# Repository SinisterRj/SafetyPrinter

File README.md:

# SafetyPrinter
This project aims to improve the safety of 3D FDM Printers by adding an external MCU (an Arduino) which increases your chance of preventing or mitigating a fire at your home.

_Safety Printer MCU assembly_

The project itself is very simple and designed to be cheap (the minimum needed is an Arduino nano and a few sensors). All you need is some time to assemble everything and test.

This project has a sibling project, the [Octoprint's Safety Printer plugin](https://github.com/SinisterRj/Octoprint_SafetyPrinter) which is optional but it's highly recommended as it helps you monitor your sensors and helps a lot during test phase:

You can find lots of information on [Wiki](https://github.com/SinisterRj/SafetyPrinter/wiki) and we recommend it's reading.

Se você é brasileiro 🇧🇷, junte-se a nós no Discord:
https://discord.gg/3DyXfGwWJY

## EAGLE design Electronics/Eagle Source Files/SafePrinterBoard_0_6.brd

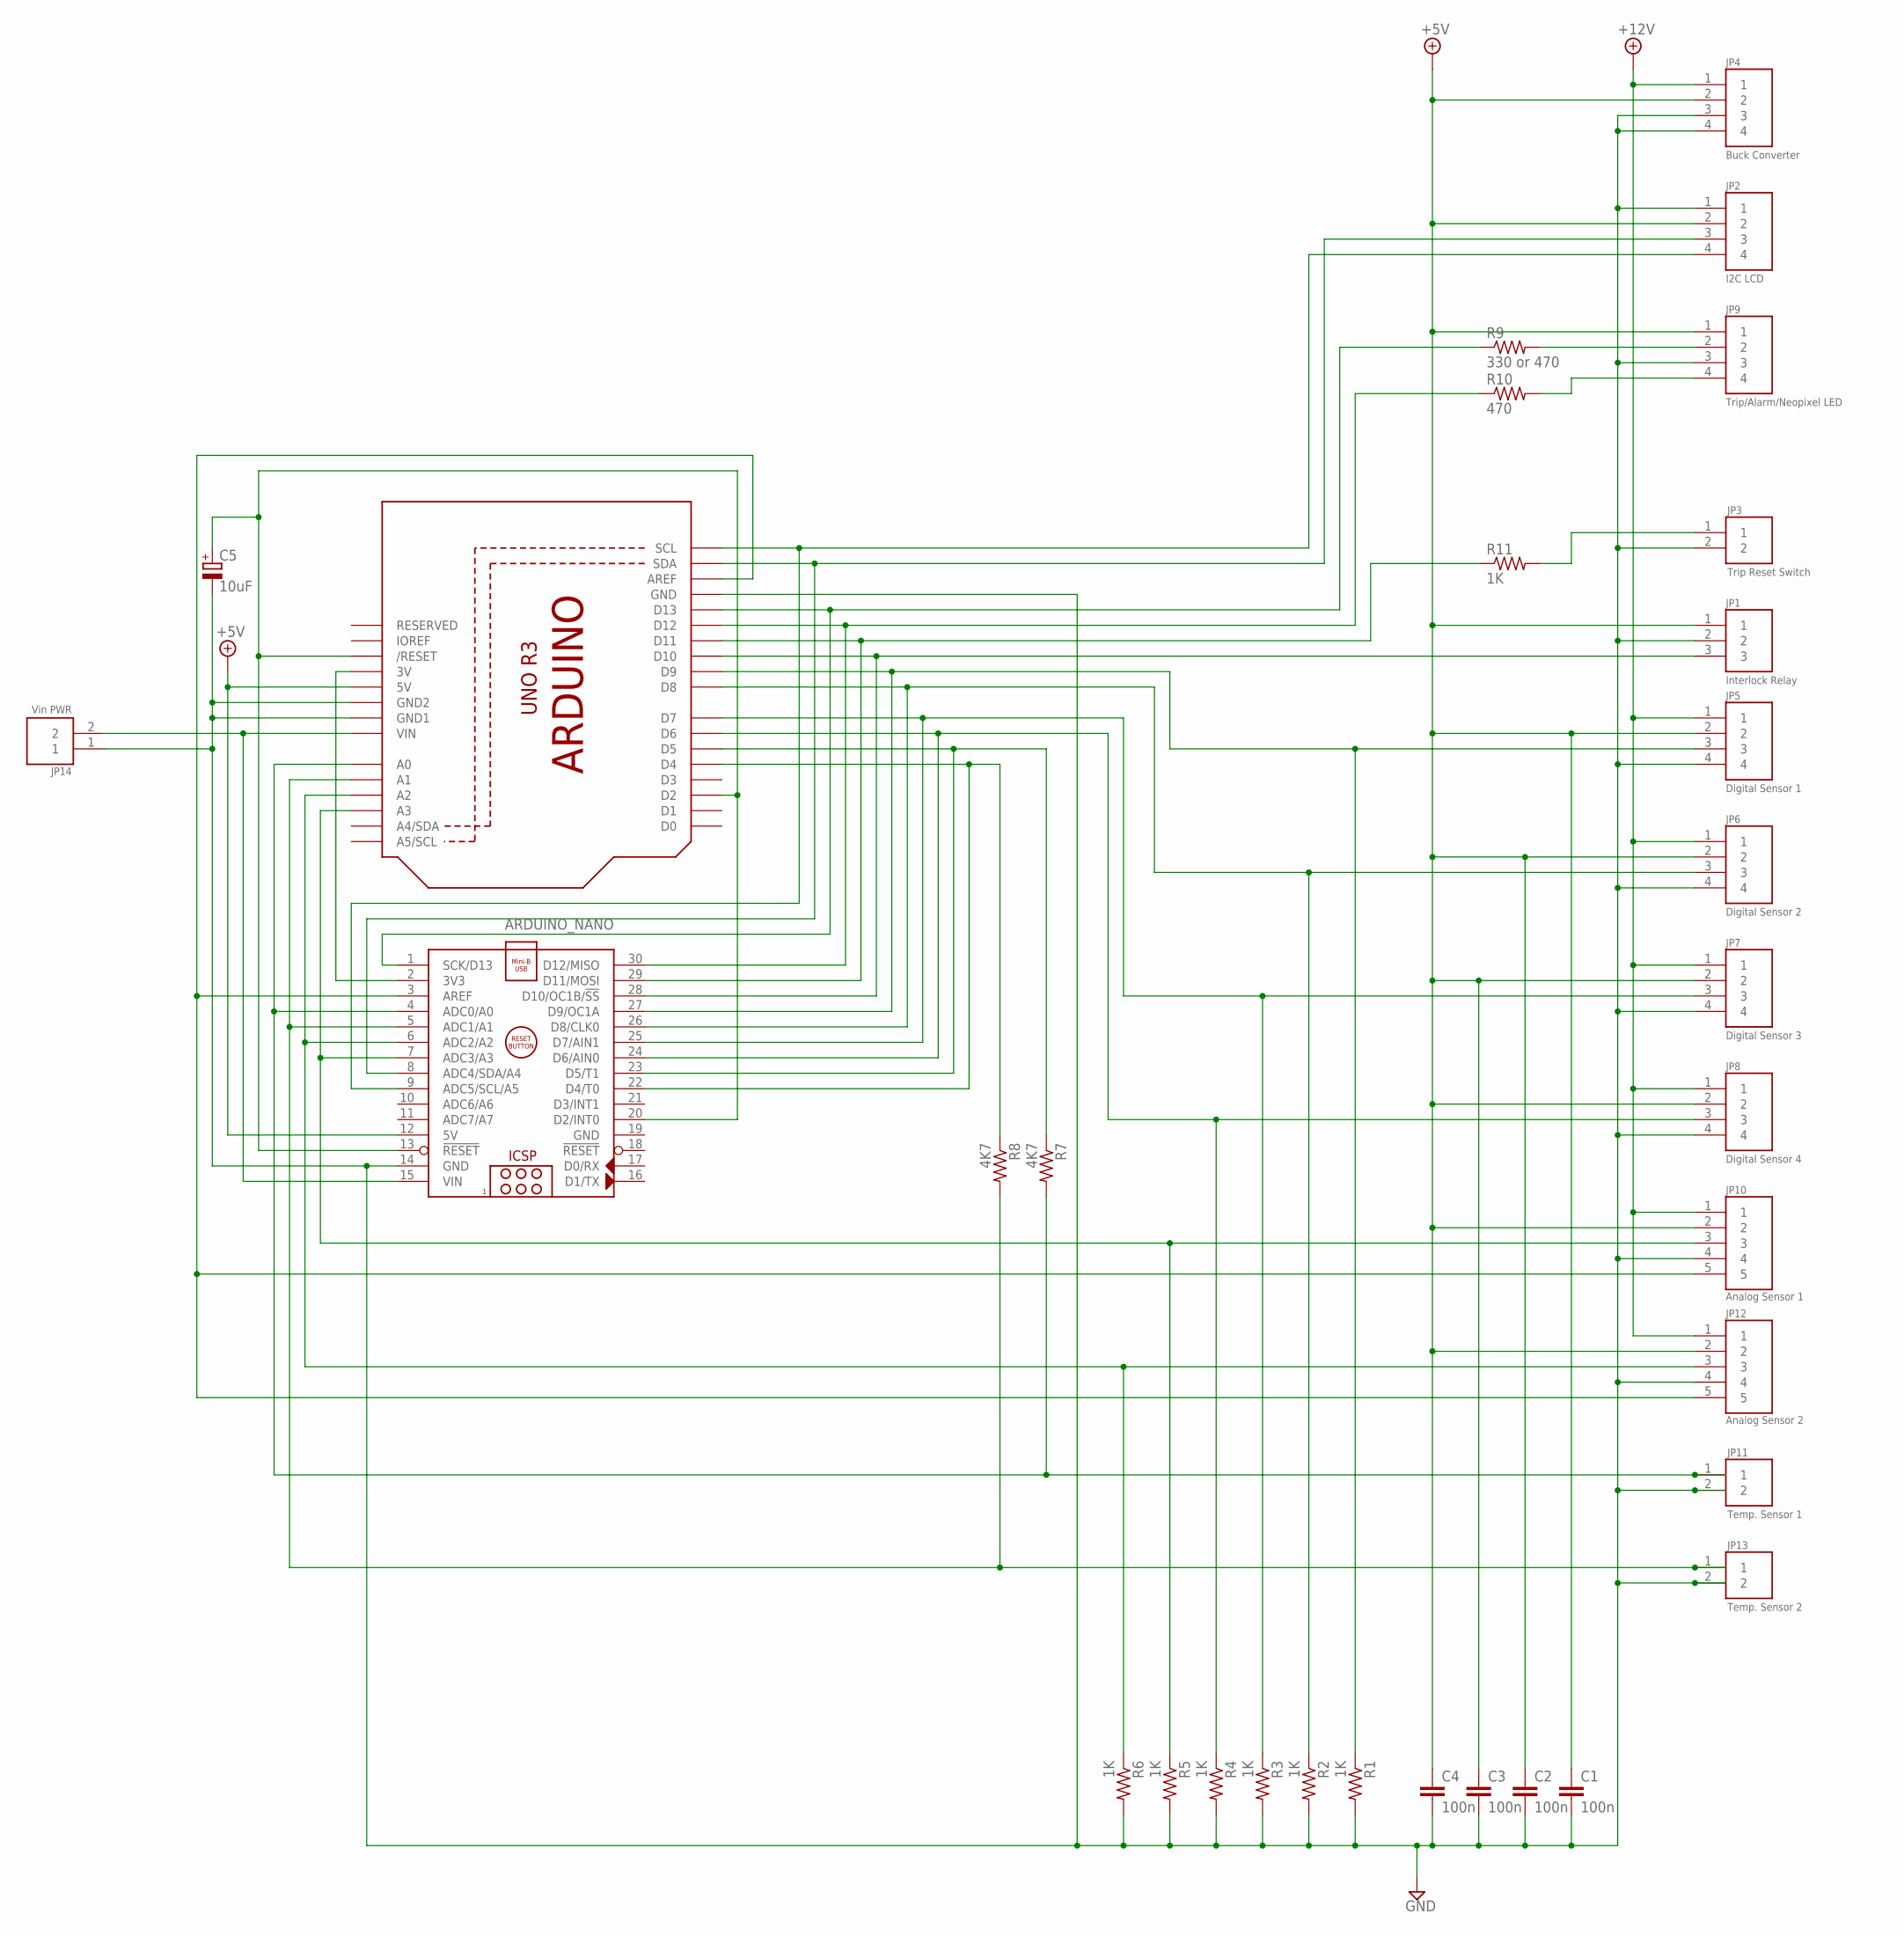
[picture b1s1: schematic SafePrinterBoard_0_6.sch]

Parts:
ARDUINO_NANO: ARDUINO_NANO
C1, C2, C3, C4: 100n; C025-025X050
C5: 10uF; E2-5
JP1: Interlock Relay; B3B-PH-K-S
JP2: I2C LCD; B4B-PH-K-S
JP3: Trip Reset Switch; B2B-PH-K-S
JP4: Buck Converter; B4B-PH-K-S
JP5: Digital Sensor 1; B4B-PH-K-S
JP6: Digital Sensor 2; B4B-PH-K-S
JP7: Digital Sensor 3; B4B-PH-K-S
JP8: Digital Sensor 4; B4B-PH-K-S
JP9: Trip/Alarm/Neopixel LED; B4B-PH-K-S
JP10: Analog Sensor 1; B5B-PH-K-S
JP11: Temp. Sensor 1; B2B-PH-K-S
JP12: Analog Sensor 2; B5B-PH-K-S
JP13: Temp. Sensor 2; B2B-PH-K-S
JP14: Vin PWR; B2B-PH-K-S
R1, R2, R3, R4, R5, R6, R11: 1K; 0805-THM
R7, R8: 4K7; 0805-THM
R9: 330 or 470; 0805-THM
R10: 470; 0805-THM
U1: ARDUINOR3-BPLACE

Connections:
+5V: ARDUINO_NANO.12 (5V), C1.1, C2.1, C3.1, C4.1, JP1.1, JP2.2, JP4.2, JP5.2, JP6.2, JP7.2, JP8.2, JP9.1, JP10.2, JP12.2, U1.5V
+12V: JP4.1, JP5.1, JP6.1, JP7.1, JP8.1, JP10.1, JP12.1
GND4: ARDUINO_NANO.14 (GND), ARDUINO_NANO.19 (GND), C1.2, C2.2, C3.2, C4.2, C5.-, JP1.2, JP2.1, JP3.2, JP4.3, JP4.4, JP5.4, JP6.4, JP7.4, JP8.4, JP9.3, JP10.4, JP11.2, JP12.4, JP13.2, JP14.1, R1.2, R2.2, R3.2, R4.2, R5.2, R6.2, U1.GND, U1.GND1, U1.GND2
unnamed: ARDUINO_NANO.28 (D10/OC1B/!SS), JP1.3, U1.D10
unnamed: ARDUINO_NANO.24 (D6/AIN0), JP8.3, R4.1, U1.D6
unnamed: JP9.2, R9.2
unnamed: ARDUINO_NANO.26 (D8/CLK0), JP6.3, R2.1, U1.D8
unnamed: ARDUINO_NANO.25 (D7/AIN1), JP7.3, R3.1, U1.D7
unnamed: ARDUINO_NANO.27 (D9/OC1A), JP5.3, R1.1, U1.D9
unnamed: ARDUINO_NANO.1 (SCK/D13), R9.1, U1.D13
unnamed: ARDUINO_NANO.30 (D12/MISO), R10.1, U1.D12
unnamed: ARDUINO_NANO.29 (D11/MOSI), R11.1, U1.D11
unnamed: ARDUINO_NANO.9 (ADC5/SCL/A5), JP2.4, U1.SCL
unnamed: ARDUINO_NANO.8 (ADC4/SDA/A4), JP2.3, U1.SDA
unnamed: ARDUINO_NANO.23 (D5/T1), R7.1, U1.D5
unnamed: JP9.4, R10.2
unnamed: ARDUINO_NANO.22 (D4/T0), R8.1, U1.D4
unnamed: ARDUINO_NANO.7 (ADC3/A3), JP10.3, R5.1, U1.A3
unnamed: ARDUINO_NANO.6 (ADC2/A2), JP12.3, R6.1, U1.A2
unnamed: ARDUINO_NANO.13 (!RESET), ARDUINO_NANO.20 (D2/INT0), C5.+, U1.D2, U1.RESET (/RESET)
unnamed: ARDUINO_NANO.15 (VIN), JP14.2, U1.VIN
unnamed: ARDUINO_NANO.4 (ADC0/A0), JP11.1, R7.2, U1.A0
unnamed: ARDUINO_NANO.5 (ADC1/A1), JP13.1, R8.2, U1.A1
unnamed: ARDUINO_NANO.3 (AREF), JP10.5, JP12.5, U1.AREF
unnamed: ARDUINO_NANO.2 (3V3), U1.3V
unnamed: JP3.1, R11.2

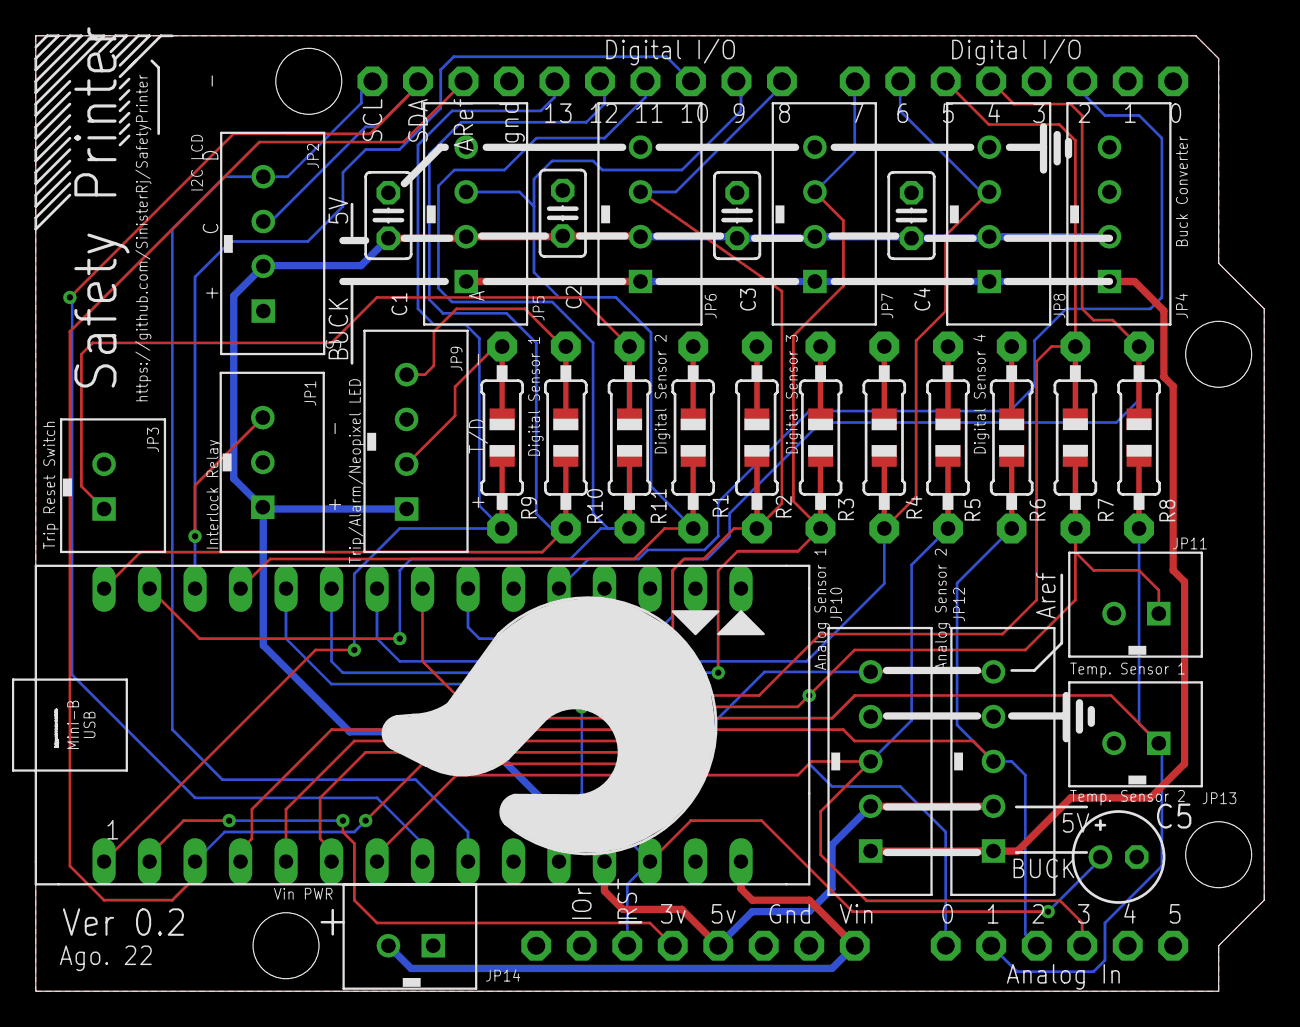
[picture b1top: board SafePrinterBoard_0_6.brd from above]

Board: 2 copper layers, 68.6 x 53.3 mm, 32 parts (0 on the bottom side), 26 nets.

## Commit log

2021-04-07 Update README.md
    First edition.
2021-04-07 Update SafetyPrinter.ino
    Change Label from "fire" to "flame"
2021-04-07 Changed folder name to - ArduinoFirmware
2021-04-27 Octoprint Plugin release
2021-04-27 No connection UI correction
2021-05-26 reorganização
2021-05-26 ver 0.2.1
    1) Include analog type of sensor to allow Hotend temperature measurement.
    2) included command <c5> to save on EEPROM sensors Enabled status and alarm set points
    3) 2 new serial commands: Remote shutdown and enable/disable sensors
    4) Now it indicates Alarm even if the sensor is disabled (but not starts de trip)
    5) Included command <r4> to return firmware version and release date
2021-05-27 General clean-up
    Solved Bug: now only send commands to arduino if user changes the set point on settings;
    Terminal Improvement: Copy more functions from octoprint terminal to focus on command line and just scrolls when tab has focus.
2021-05-28 Auto serial port improvement
    Plugin don't connect if the default serial port is AUTO and the printer is not connected to avoid it to connect to the printer instead of the safety printer MCU. Also the default serial port combo bo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
2021-05-28 Update version number
2021-05-28 Include: Hot End NTC Sensor
2021-05-29 Ver. 0.2.2
    * Version 0.2.2
    * Changes:
    * 1) Defined limits for set point definition.
    * 2) Now EEPROM read uses the addr 0 as a version flag. If it is different from EEPROMVERSION (because new release changed EEPROM structure), the firmware will overwrite it.
2021-05-29 Add Terminal filter
    extra: Remove "termios" library from connection.py
2021-05-30 Fixed windows COM identification
2021-05-31 Sidebar style update, including icons
2021-06-01 Shutdown after finish printing.
2021-06-01 Include C6 command for turn on/off printer
    Comands arguments now are case insensitive.
2021-06-04 Include C7 and C8 commands and Octoprint Plugin just apply changes when user saves.
2021-07-29 Version 0.2.3
    Firmware:
    1) Fix a bug when reading EEPROM data.
    2) Split project into multiple files.
    3) Checks EEPROM for CRC.
    4) Update <c4> command to send EEPROM and Serial Protocol versions
    Plugin:
2021-07-29 Update configuration tips.
2021-07-30 0.2.4
    1) Include Marlin Thermistor files for better thermistor configuration;
    2) Configuration.h created.
2021-08-01 Include Bed Temp. NTC sensor
2021-08-05 Better connection and error notifications
    1) Improves printer comm. port identification and dealing. Now don't show printer port on plugin settings.
    2) Implements pop up notifications for all error messages.
    3) Logging all levels.
2021-08-30 Color UI Customizer Compatibility
2021-08-30 Release 1.0.0 version
2021-08-30 Moved Octoprint Plugin
    Moved Octoprint Plugin to specific repo: https://github.com/SinisterRj/Octoprint_SafetyPrinter
2021-09-10 Version 0.2.5
    1) Include CRC check on <r1>,<r2> and <r4> responses;
    2) Organize some thermisotr tables and Configuration.h file;
    3) Check for some errors on sensor configuration and disable it.
    4) Include commands alias;
    5) Include free memory, voltage, temperature and cycle time monitoring;
2021-10-21 0.2.5b
    6) Include I2C 16x2 LCD support
    7) Creates "lowSP" and "highSP" sensor values (now user can choose different sensors);
    8) <R2> now sends "forceEnable", "lowSP" and "highSP" values;
    9) Include a timer to avoid sucessive trips/resets or turns on/off on printer and damage it.
2021-10-21 0.2.5b
    Include LCD
2021-10-22 0.2.5c
    Check for compiling without optionals.
2021-10-27 Fix LCD GND and VCC conections
    Fix LCD GND and VCC conections;
    Include MT3608 module name to buck converter.
2022-03-01 Added r6 command to check printerPowered status
2022-03-11 1.1.1rc1
    1.1.1rc1
2022-03-11 Revert "0.2.6a"
2022-03-28 Added ping command to serial line
2022-08-30 0.2.6rc1
    30/08/22
    Changes:
    1) New default pin out to match with the official Safety Printer Arduino Shield;
    2) Include <R6> command to repeat intro msg;
    3) Remove "booting..." string from the setup;
    4) Auto detects different Arduino boards;
2022-08-30 Board Ver 0.6
    1) Adds capacitor to avoid autoreset upon serial connection;
    2) Removes UART connector;
    3) Adds neopixel support for alarm and trip LEDs;
    4) Removes some unused holes;
    5) Rearranges some connectors to avoid Arduino UNO USB connector short circuit.
2022-09-26 Add notes to schematics
2022-09-27 Fix Neopixel pin
2022-09-27 Update version/release date
2022-10-13 0.2.7
    1) Monitors RESET button to a continuous operation (shortcircuited) and disables it to avoid auto reset after a trip.
2022-10-23 0.2.7
